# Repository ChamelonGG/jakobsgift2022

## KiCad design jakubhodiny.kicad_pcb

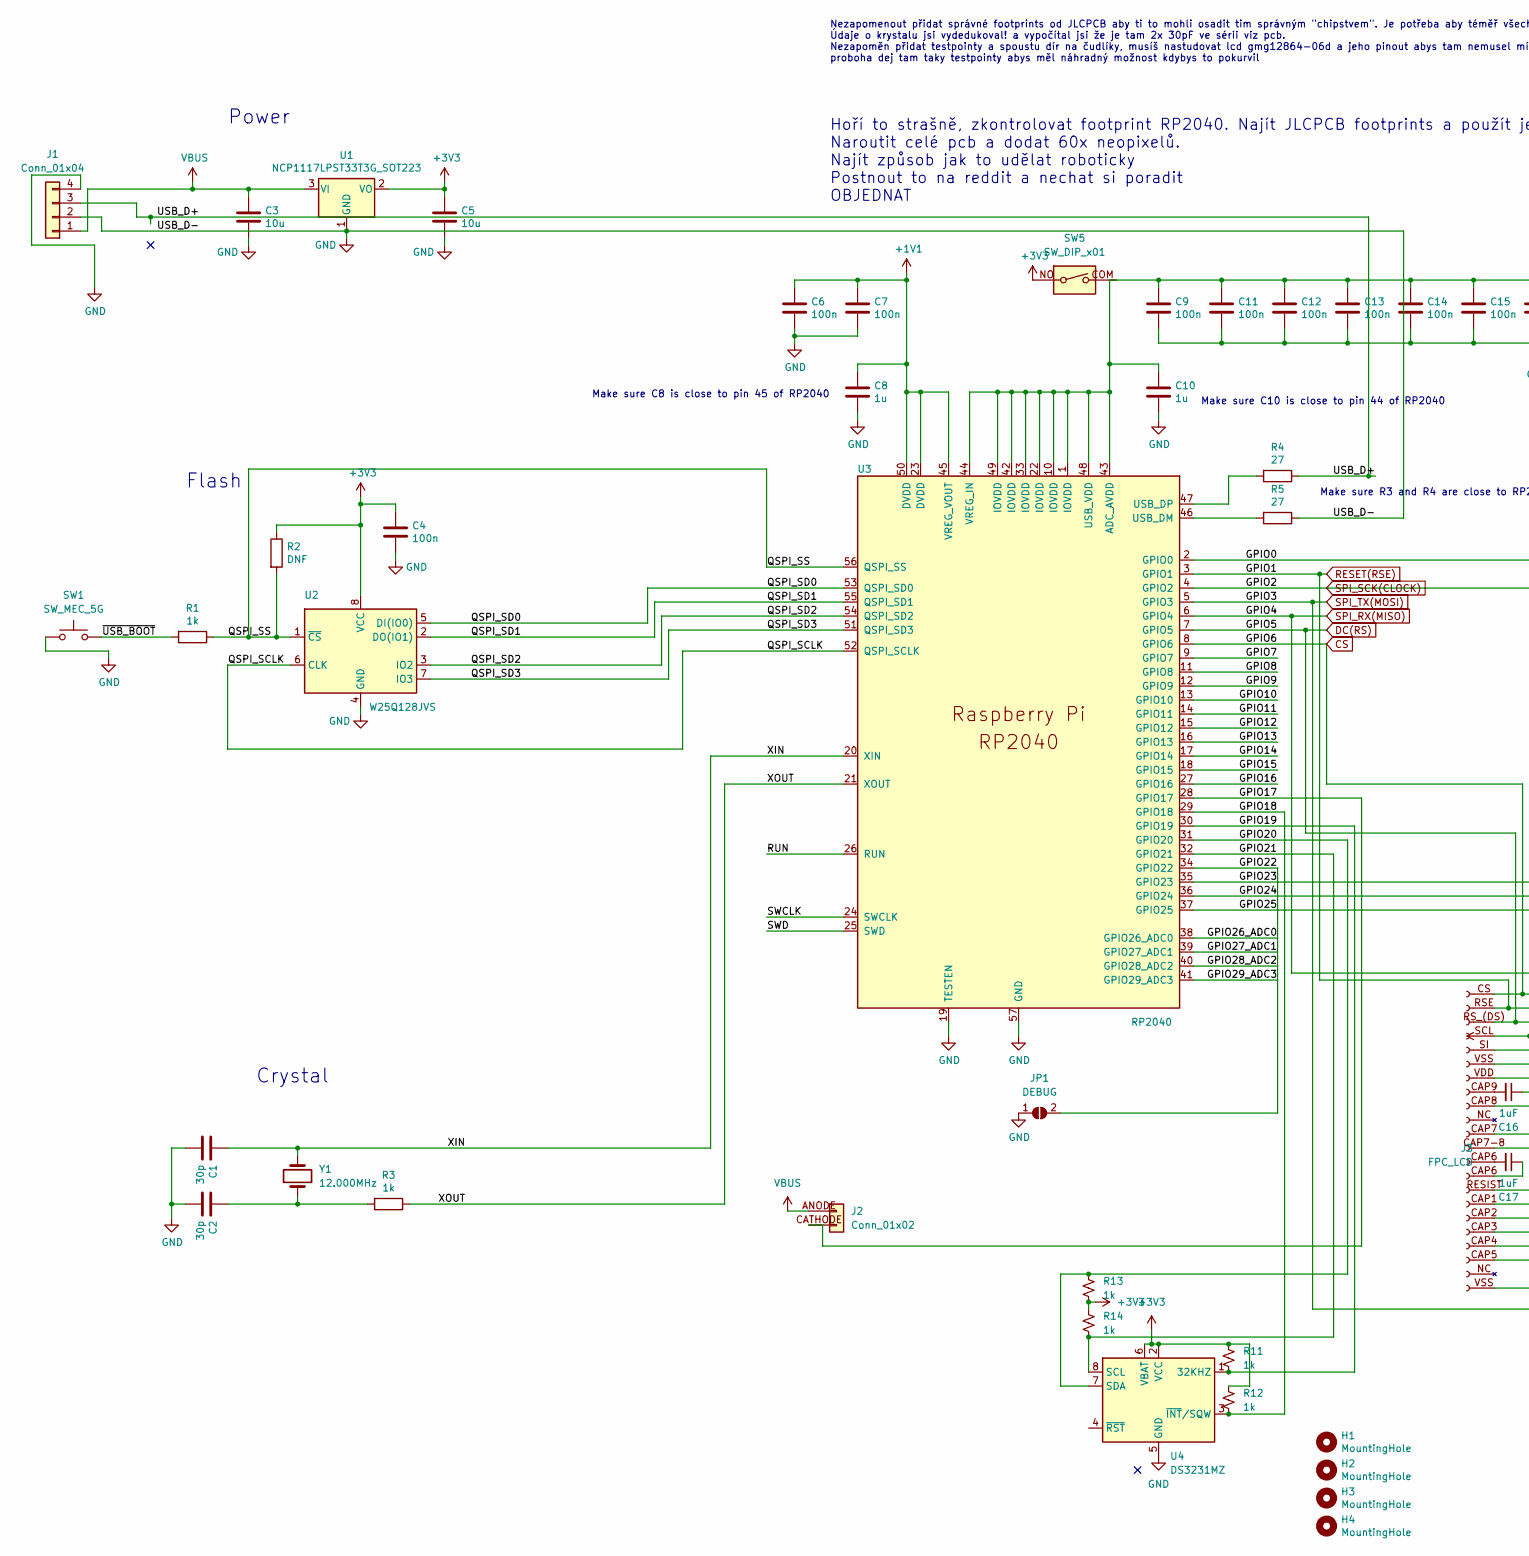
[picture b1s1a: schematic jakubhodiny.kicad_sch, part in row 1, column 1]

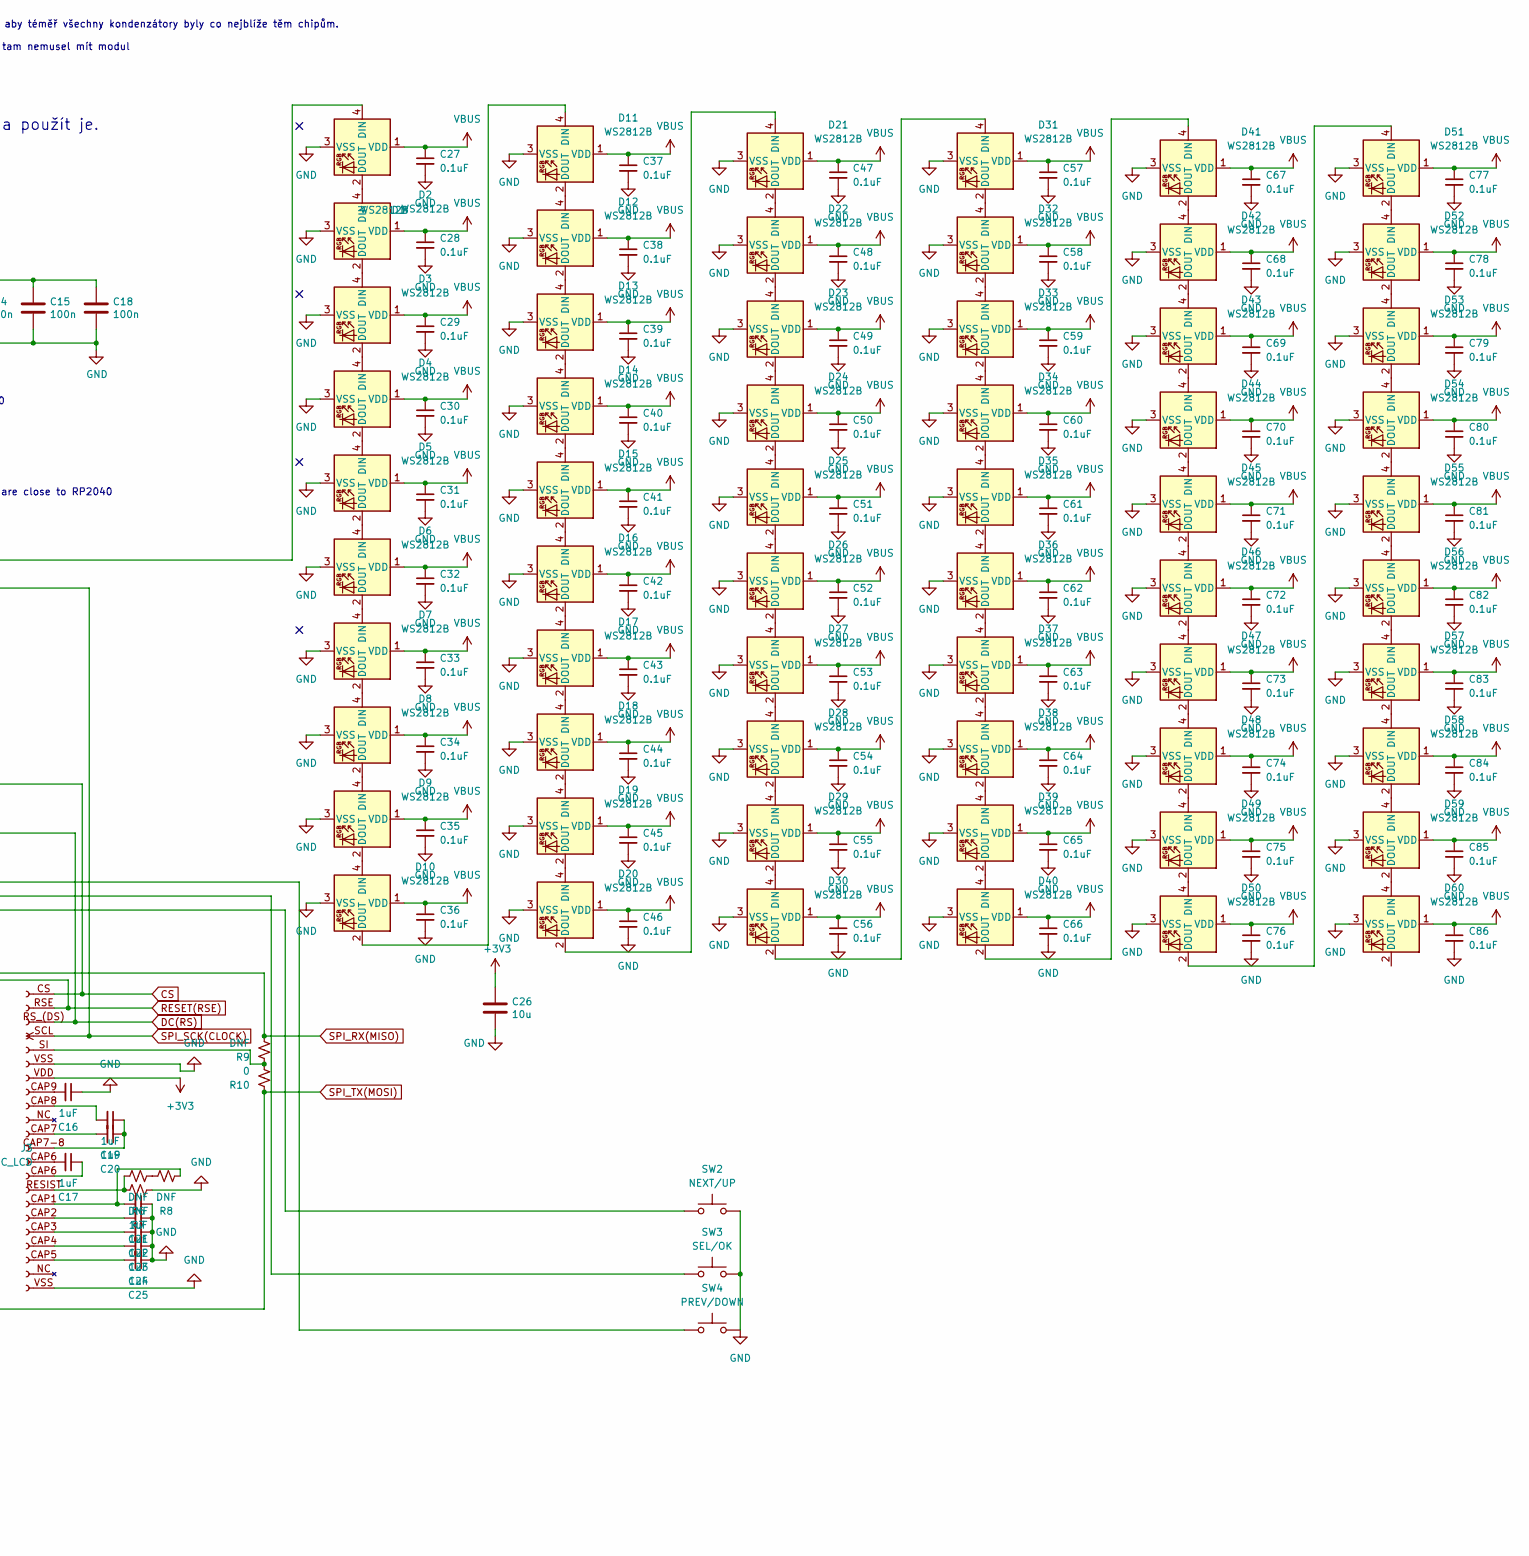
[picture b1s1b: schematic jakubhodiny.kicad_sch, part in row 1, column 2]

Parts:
C1, C2: 30p; C_0402_1005Metric
C3, C5, C26: 10u; C_0805_2012Metric
C4, C6, C7, C9, C11, C12, C13, C14, C15, C18: 100n; C_0402_1005Metric
C8, C10: 1u; C_0402_1005Metric
C16, C17, C19, C20, C21, C22, C23, C24, C25: 1uF; C_0402_1005Metric
C27, C28, C29, C30, C31, C32, C33, C34, C35, C36, C37, C38, C39, C40, C41, C42, C43, C44, C45, C46, C47, C48, C49, C50, C51, C52, C53, C54, C55, C56, C57, C58, C59, C60, C61, C62, C63, C64, C65, C66, C67, C68, C69, C70, C71, C72, C73, C74, C75, C76, C77, C78, C79, C80, C81, C82, C83, C84, C85, C86: 0.1uF; C_0402_1005Metric
D1, D2, D3, D4, D5, D6, D7, D8, D9, D10, D11, D12, D13, D14, D15, D16, D17, D18, D19, D20, D21, D22, D23, D24, D25, D26, D27, D28, D29, D30, D31, D32, D33, D34, D35, D36, D37, D38, D39, D40, D41, D42, D43, D44, D45, D46, D47, D48, D49, D50, D51, D52, D53, D54, D55, D56, D57, D58, D59, D60: WS2812B; LED_WS2812B_PLCC4_5.0x5.0mm_P3.2mm
H1, H2, H3, H4: MountingHole; MountingHole_2.7mm_M2.5
J1: Conn_01x04; PinHeader_1x04_P2.54mm_Horizontal
J2: Conn_01x02; BACKLIGHT_LCD
J3: FPC_LCD; FCP_LCD
JP1: DEBUG; SolderJumper-2_P1.3mm_Open_Pad1.0x1.5mm
R1, R3: 1k; C_0402_1005Metric
R2: DNF; C_0402_1005Metric
R4, R5: 27; C_0402_1005Metric
R6, R7, R8, R9: DNF; SolderJumper-2_P1.3mm_Open_Pad1.0x1.5mm
R10: 0; SolderJumper-2_P1.3mm_Bridged2Bar_Pad1.0x1.5mm
R11, R12, R13, R14: 1k; R_0402_1005Metric
SW1: SW_MEC_5G; SW_PUSH_6mm
SW2: NEXT/UP; SW_PUSH_6mm
SW3: SEL/OK; SW_PUSH_6mm
SW4: PREV/DOWN; SW_PUSH_6mm
SW5: SW_DIP_x01; pushswitch
U1: NCP1117LPST33T3G_SOT223; SOT-223-3_TabPin2
U2: W25Q128JVS; SOIC-8_5.23x5.23mm_P1.27mm
U3: RP2040; RP2040-QFN-56
U4: DS3231MZ; SOIC-8_3.9x4.9mm_P1.27mm
Y1: 12.000MHz; Crystal_SMD_HC49-SD_HandSoldering

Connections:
+1V1: C6.1, C7.1, C8.1, U3.23 (DVDD), U3.45 (VREG_VOUT), U3.50 (DVDD)
+3V3: C4.1, C5.1, C26.1, J3.VDD (16), R2.1, R11.1, R12.1, R13.1, R14.1, SW5.NO, U1.2 (VO), U2.8 (VCC), U4.2 (VCC), U4.6 (VBAT)
/GPIO0: D1.4 (DIN), U3.2 (GPIO0)
/GPIO7: U3.9 (GPIO7)
/GPIO8: U3.11 (GPIO8)
/GPIO9: U3.12 (GPIO9)
/GPIO10: U3.13 (GPIO10)
/GPIO11: U3.14 (GPIO11)
/GPIO12: U3.15 (GPIO12)
/GPIO13: U3.16 (GPIO13)
/GPIO14: U3.17 (GPIO14)
/GPIO15: U3.18 (GPIO15)
/GPIO16: U3.27 (GPIO16)
/GPIO17: J2.CATHODE (Pin_2), U3.28 (GPIO17)
/GPIO18: R12.2, U3.29 (GPIO18), U4.3 (~INT/SQW)
/GPIO19: R11.2, U3.30 (GPIO19), U4.1 (32KHZ)
/GPIO20: R13.2, U3.31 (GPIO20), U4.7 (SDA)
/GPIO21: R14.2, U3.32 (GPIO21), U4.8 (SCL)
/QSPI_SCLK: U2.6 (CLK), U3.52 (QSPI_SCLK)
/QSPI_SD0: U2.5 (DI(IO0)), U3.53 (QSPI_SD0)
/QSPI_SD1: U2.2 (DO(IO1)), U3.55 (QSPI_SD1)
/QSPI_SD2: U2.3 (IO2), U3.54 (QSPI_SD2)
/QSPI_SD3: U2.7 (IO3), U3.51 (QSPI_SD3)
/QSPI_SS: R1.1, R2.2, U2.1 (~CS), U3.56 (QSPI_SS)
/RUN: U3.26 (RUN)
/SWCLK: U3.24 (SWCLK)
/SWD: U3.25 (SWD)
/USB_D+: J1.3, R4.1
/XIN: C1.1, U3.20 (XIN), Y1.2
/XOUT: R3.1, U3.21 (XOUT)
/~USB_BOOT: R1.2, SW1.3 (B), SW1.4 (B)
CS: J3.CS (22), U3.8 (GPIO6)
DC(RS): J3.RS_(DS) (20), U3.7 (GPIO5)
GND: C1.2, C2.2, C3.2, C4.2, C5.2, C6.2, C7.2, C8.2, C9.2, C10.2, C11.2, C12.2, C13.2, C14.2, C15.2, C16.1, C18.2, C21.1, C22.1, C23.1, C24.1, C25.1, C26.2, C27.2, C28.2, C29.2, C30.2, C31.2, C32.2, C33.2, C34.2, C35.2, C36.2, C37.2, C38.2, C39.2, C40.2, C41.2, C42.2, C43.2, C44.2, C45.2, C46.2, C47.2, C48.2, C49.2, C50.2, C51.2, C52.2, C53.2, C54.2, C55.2, C56.2, C57.2, C58.2, C59.2, C60.2, C61.2, C62.2, C63.2, C64.2, C65.2, C66.2, C67.2, C68.2, C69.2, C70.2, C71.2, C72.2, C73.2, C74.2, C75.2, C76.2, C77.2, C78.2, C79.2, C80.2, C81.2, C82.2, C83.2, C84.2, C85.2, C86.2, D1.3 (VSS), D2.3 (VSS), D3.3 (VSS), D4.3 (VSS), D5.3 (VSS), D6.3 (VSS), D7.3 (VSS), D8.3 (VSS), D9.3 (VSS), D10.3 (VSS), D11.3 (VSS), D12.3 (VSS), D13.3 (VSS), D14.3 (VSS), D15.3 (VSS), D16.3 (VSS), D17.3 (VSS), D18.3 (VSS), D19.3 (VSS), D20.3 (VSS), D21.3 (VSS), D22.3 (VSS), D23.3 (VSS), D24.3 (VSS), D25.3 (VSS), D26.3 (VSS), D27.3 (VSS), D28.3 (VSS), D29.3 (VSS), D30.3 (VSS), D31.3 (VSS), D32.3 (VSS), D33.3 (VSS), D34.3 (VSS), D35.3 (VSS), D36.3 (VSS), D37.3 (VSS), D38.3 (VSS), D39.3 (VSS), D40.3 (VSS), D41.3 (VSS), D42.3 (VSS), D43.3 (VSS), D44.3 (VSS), D45.3 (VSS), D46.3 (VSS), D47.3 (VSS), D48.3 (VSS), D49.3 (VSS), D50.3 (VSS), D51.3 (VSS), D52.3 (VSS), D53.3 (VSS), D54.3 (VSS), D55.3 (VSS), D56.3 (VSS), D57.3 (VSS), D58.3 (VSS), D59.3 (VSS), D60.3 (VSS), J1.2, J1.4, J3.VSS (17), JP1.1 (A), R5.1, R7.2, SW1.1 (A), SW1.2 (A), SW2.3 (B), SW2.4 (B), SW3.3 (B), SW3.4 (B), SW4.3 (B), SW4.4 (B), U1.1 (GND), U2.4 (GND), U3.19 (TESTEN), U3.57 (GND), U4.5 (GND)
unnamed: C2.1, R3.2, Y1.1
unnamed: C9.1, C10.1, C11.1, C12.1, C13.1, C14.1, C15.1, C18.1, U3.1 (IOVDD), U3.10 (IOVDD), U3.22 (IOVDD), U3.33 (IOVDD), U3.42 (IOVDD), U3.43 (ADC_AVDD), U3.44 (VREG_IN), U3.48 (USB_VDD), U3.49 (IOVDD)
unnamed: C16.2, J3.CAP9 (15)
unnamed: C19.1, C20.1, J3.CAP7-8 (11)
unnamed: C19.2, J3.CAP8 (14)
unnamed: C20.2, J3.CAP7 (12)
unnamed: C21.2, J3.CAP1 (7), R8.2
unnamed: C22.2, J3.CAP2 (6)
unnamed: C23.2, J3.CAP3 (5)
unnamed: C24.2, J3.CAP4 (4)
unnamed: C25.2, J3.CAP5 (3)
unnamed: D1.2 (DOUT), D2.4 (DIN)
unnamed: D2.2 (DOUT), D3.4 (DIN)
unnamed: D3.2 (DOUT), D4.4 (DIN)
unnamed: D4.2 (DOUT), D5.4 (DIN)
unnamed: D5.2 (DOUT), D6.4 (DIN)
unnamed: D6.2 (DOUT), D7.4 (DIN)
unnamed: D7.2 (DOUT), D8.4 (DIN)
unnamed: D8.2 (DOUT), D9.4 (DIN)
unnamed: D10.2 (DOUT), D11.4 (DIN)
unnamed: D9.2 (DOUT), D10.4 (DIN)
unnamed: D11.2 (DOUT), D12.4 (DIN)
unnamed: D12.2 (DOUT), D13.4 (DIN)
unnamed: D13.2 (DOUT), D14.4 (DIN)
unnamed: D14.2 (DOUT), D15.4 (DIN)
unnamed: D15.2 (DOUT), D16.4 (DIN)
unnamed: D16.2 (DOUT), D17.4 (DIN)
unnamed: D17.2 (DOUT), D18.4 (DIN)
unnamed: D18.2 (DOUT), D19.4 (DIN)
unnamed: D19.2 (DOUT), D20.4 (DIN)
unnamed: D20.2 (DOUT), D21.4 (DIN)
unnamed: D21.2 (DOUT), D22.4 (DIN)
unnamed: D22.2 (DOUT), D23.4 (DIN)
unnamed: D23.2 (DOUT), D24.4 (DIN)
unnamed: D24.2 (DOUT), D25.4 (DIN)
unnamed: D25.2 (DOUT), D26.4 (DIN)
unnamed: D26.2 (DOUT), D27.4 (DIN)
unnamed: D27.2 (DOUT), D28.4 (DIN)
unnamed: D28.2 (DOUT), D29.4 (DIN)
unnamed: D29.2 (DOUT), D30.4 (DIN)
unnamed: D30.2 (DOUT), D31.4 (DIN)
unnamed: D31.2 (DOUT), D32.4 (DIN)
unnamed: D32.2 (DOUT), D33.4 (DIN)
unnamed: D33.2 (DOUT), D34.4 (DIN)
unnamed: D34.2 (DOUT), D35.4 (DIN)
unnamed: D35.2 (DOUT), D36.4 (DIN)
unnamed: D36.2 (DOUT), D37.4 (DIN)
unnamed: D37.2 (DOUT), D38.4 (DIN)
unnamed: D38.2 (DOUT), D39.4 (DIN)
unnamed: D39.2 (DOUT), D40.4 (DIN)
unnamed: D40.2 (DOUT), D41.4 (DIN)
unnamed: D41.2 (DOUT), D42.4 (DIN)
unnamed: D42.2 (DOUT), D43.4 (DIN)
unnamed: D43.2 (DOUT), D44.4 (DIN)
unnamed: D44.2 (DOUT), D45.4 (DIN)
unnamed: D45.2 (DOUT), D46.4 (DIN)
unnamed: D46.2 (DOUT), D47.4 (DIN)
unnamed: D47.2 (DOUT), D48.4 (DIN)
unnamed: D48.2 (DOUT), D49.4 (DIN)
unnamed: D49.2 (DOUT), D50.4 (DIN)
unnamed: D50.2 (DOUT), D51.4 (DIN)
unnamed: D51.2 (DOUT), D52.4 (DIN)
unnamed: D52.2 (DOUT), D53.4 (DIN)
unnamed: D53.2 (DOUT), D54.4 (DIN)
unnamed: D54.2 (DOUT), D55.4 (DIN)
unnamed: D55.2 (DOUT), D56.4 (DIN)
unnamed: D56.2 (DOUT), D57.4 (DIN)
unnamed: D57.2 (DOUT), D58.4 (DIN)
unnamed: D58.2 (DOUT), D59.4 (DIN)
unnamed: D59.2 (DOUT), D60.4 (DIN)
unnamed: J3.RESIST (8), R6.1, R7.1
unnamed: J3.SI (18), R9.1, R10.2
unnamed: R4.2, U3.47 (USB_DP)
unnamed: R5.2, U3.46 (USB_DM)
unnamed: R6.2, R8.1
RESET(RSE): J3.RSE (21), U3.3 (GPIO1)
SPI_RX(MISO): R9.2, U3.6 (GPIO4)
SPI_SCK(CLOCK): J3.SCL (19), U3.4 (GPIO2)
SPI_TX(MOSI): R10.1, U3.5 (GPIO3)
VBUS: C3.1, C27.1, C28.1, C29.1, C30.1, C31.1, C32.1, C33.1, C34.1, C35.1, C36.1, C37.1, C38.1, C39.1, C40.1, C41.1, C42.1, C43.1, C44.1, C45.1, C46.1, C47.1, C48.1, C49.1, C50.1, C51.1, C52.1, C53.1, C54.1, C55.1, C56.1, C57.1, C58.1, C59.1, C60.1, C61.1, C62.1, C63.1, C64.1, C65.1, C66.1, C67.1, C68.1, C69.1, C70.1, C71.1, C72.1, C73.1, C74.1, C75.1, C76.1, C77.1, C78.1, C79.1, C80.1, C81.1, C82.1, C83.1, C84.1, C85.1, C86.1, D1.1 (VDD), D2.1 (VDD), D3.1 (VDD), D4.1 (VDD), D5.1 (VDD), D6.1 (VDD), D7.1 (VDD), D8.1 (VDD), D9.1 (VDD), D10.1 (VDD), D11.1 (VDD), D12.1 (VDD), D13.1 (VDD), D14.1 (VDD), D15.1 (VDD), D16.1 (VDD), D17.1 (VDD), D18.1 (VDD), D19.1 (VDD), D20.1 (VDD), D21.1 (VDD), D22.1 (VDD), D23.1 (VDD), D24.1 (VDD), D25.1 (VDD), D26.1 (VDD), D27.1 (VDD), D28.1 (VDD), D29.1 (VDD), D30.1 (VDD), D31.1 (VDD), D32.1 (VDD), D33.1 (VDD), D34.1 (VDD), D35.1 (VDD), D36.1 (VDD), D37.1 (VDD), D38.1 (VDD), D39.1 (VDD), D40.1 (VDD), D41.1 (VDD), D42.1 (VDD), D43.1 (VDD), D44.1 (VDD), D45.1 (VDD), D46.1 (VDD), D47.1 (VDD), D48.1 (VDD), D49.1 (VDD), D50.1 (VDD), D51.1 (VDD), D52.1 (VDD), D53.1 (VDD), D54.1 (VDD), D55.1 (VDD), D56.1 (VDD), D57.1 (VDD), D58.1 (VDD), D59.1 (VDD), D60.1 (VDD), J1.1, J2.ANODE (Pin_1), U1.3 (VI)

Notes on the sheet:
Make sure C10 is close to pin 44 of RP2040
Crystal
Make sure R3 and R4 are close to RP2040
Flash
Nezapomenout přidat správné footprints od JLCPCB aby ti to mohli osadit tim správným "chipstvem". Je potřeba aby téměř všechny kondenzátory byly co nejblíže těm chipům. Údaje o krystalu jsi vydedukoval! a vypočítal jsi že je tam 2x 30pF ve sérii viz pcb. Nezapoměn přidat testpointy a spoustu dír na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
Make sure C8 is close to pin 45 of RP2040
Hoří to strašně, zkontrolovat footprint RP2040. Najít JLCPCB footprints a použít je. Naroutit celé pcb a dodat 60x neopixelů. Najít způsob jak to udělat roboticky Postnout to na reddit a nechat si poradit OBJEDNAT
Power

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
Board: 2 copper layers, 178 parts (0 on the bottom side), 105 nets, no tracks yet.

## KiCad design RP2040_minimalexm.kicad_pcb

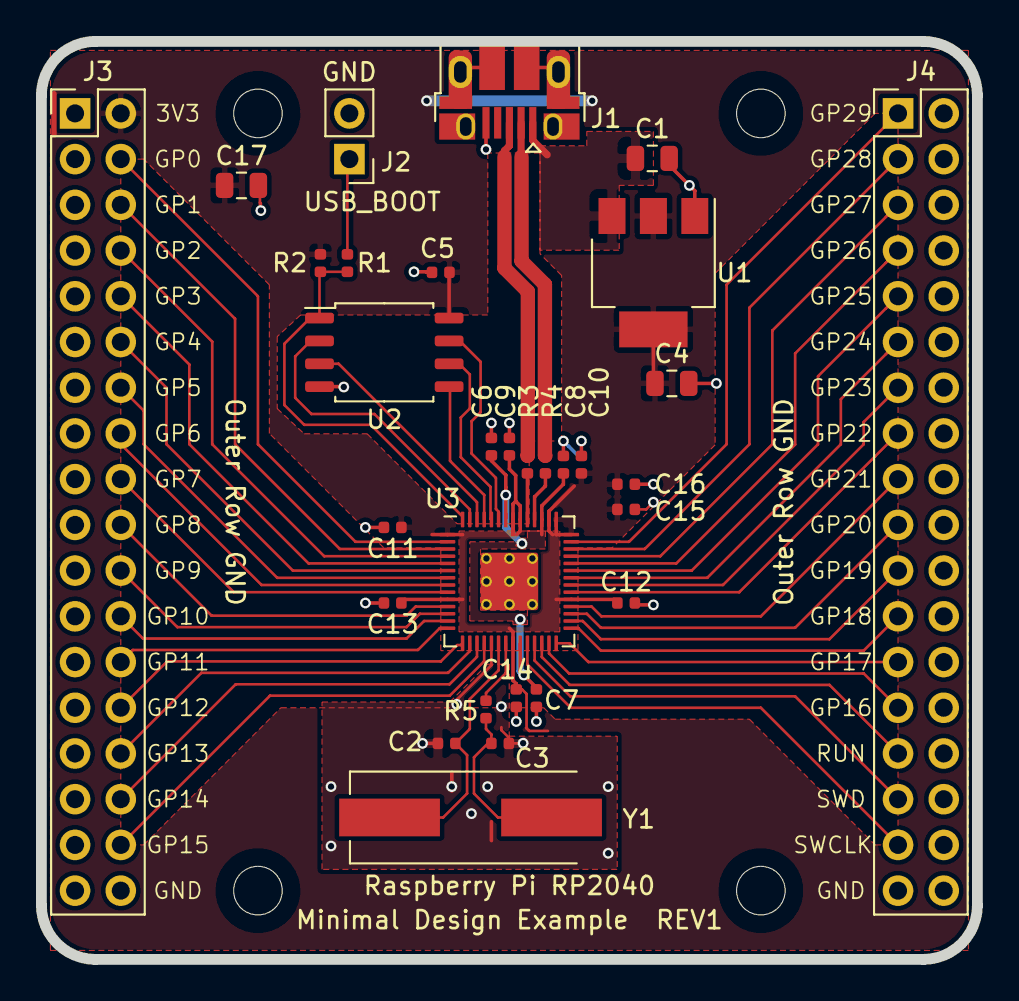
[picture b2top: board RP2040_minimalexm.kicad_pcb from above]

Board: 2 copper layers, 52.0 x 51.0 mm, 34 parts (0 on the bottom side), 51 nets.

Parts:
C1, C4, C17: 10u; C_0805_2012Metric
C2, C3: 27p; C_0402_1005Metric
C5, C6, C7, C9, C11, C12, C13, C14, C15, C16: 100n; C_0402_1005Metric
C8, C10: 1u; C_0402_1005Metric
H1, H2, H3, H4: MountingHole; MountingHole_2.7mm_M2.5
J1: USB_B_Micro; USB_Micro-B_Amphenol_10103594-0001LF_Horizontal_modified
J2: Conn_01x02; PinHeader_1x02_P2.54mm_Vertical
J3, J4: Conn_02x18_Odd_Even; PinHeader_2x18_P2.54mm_Vertical
R1, R5: 1k; C_0402_1005Metric
R2: DNF; C_0402_1005Metric
R3, R4: 27; C_0402_1005Metric
U1: NCP1117-3.3_SOT223; SOT-223-3_TabPin2
U2: W25Q128JVS; SOIC-8_5.23x5.23mm_P1.27mm
U3: RP2040; RP2040-QFN-56
Y1: ABLS-12.000MHZ-B4-T; Crystal_SMD_HC49-US

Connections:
+1V1: C6.1, C7.1, C8.1, U3.23, U3.45, U3.50
+3V3: C4.1, C5.1, C9.1, C10.1, C11.1, C12.1, C13.1, C14.1, C15.1, C16.1, C17.1, J3.2, R2.1, U1.2, U2.8, U3.1, U3.10, U3.22, U3.33, U3.42, U3.43, U3.44, U3.48, U3.49
/GPIO0: J3.4, U3.2
/GPIO1: J3.6, U3.3
/GPIO2: J3.8, U3.4
/GPIO3: J3.10, U3.5
/GPIO4: J3.12, U3.6
/GPIO5: J3.14, U3.7
/GPIO6: J3.16, U3.8
/GPIO7: J3.18, U3.9
/GPIO8: J3.20, U3.11
/GPIO9: J3.22, U3.12
/GPIO10: J3.24, U3.13
/GPIO11: J3.26, U3.14
/GPIO12: J3.28, U3.15
/GPIO13: J3.30, U3.16
/GPIO14: J3.32, U3.17
/GPIO15: J3.34, U3.18
/GPIO16: J4.27, U3.27
/GPIO17: J4.25, U3.28
/GPIO18: J4.23, U3.29
/GPIO19: J4.21, U3.30
/GPIO20: J4.19, U3.31
/GPIO21: J4.17, U3.32
/GPIO22: J4.15, U3.34
/GPIO23: J4.13, U3.35
/GPIO24: J4.11, U3.36
/GPIO25: J4.9, U3.37
/GPIO26_ADC0: J4.7, U3.38
/GPIO27_ADC1: J4.5, U3.39
/GPIO28_ADC2: J4.3, U3.40
/GPIO29_ADC3: J4.1, U3.41
/QSPI_SCLK: U2.6, U3.52
/QSPI_SD0: U2.5, U3.53
/QSPI_SD1: U2.2, U3.55
/QSPI_SD2: U2.3, U3.54
/QSPI_SD3: U2.7, U3.51
/QSPI_SS: R1.1, R2.2, U2.1, U3.56
/RUN: J4.29, U3.26
/SWCLK: J4.33, U3.24
/SWD: J4.31, U3.25
/USB_D+: J1.3, R3.1
/USB_D-: J1.2, R4.1
/XIN: C2.1, U3.20, Y1.1
/XOUT: R5.1, U3.21
/~USB_BOOT: J2.1, R1.2
GND: C1.2, C2.2, C3.2, C4.2, C5.2, C6.2, C7.2, C8.2, C9.2, C10.2, C11.2, C12.2, C13.2, C14.2, C15.2, C16.2, C17.2, J1.5, J1.6, J2.2, J3.1, J3.3, J3.5, J3.7, J3.9, J3.11, J3.13, J3.15, J3.17, J3.19, J3.21, J3.23, J3.25, J3.27, J3.29, J3.31, J3.33, J3.35, J3.36, J4.2, J4.4, J4.6, J4.8, J4.10, J4.12, J4.14, J4.16, J4.18, J4.20, J4.22, J4.24, J4.26, J4.28, J4.30, J4.32, J4.34, J4.35, J4.36, U1.1, U2.4, U3.19, U3.57
unnamed: C3.1, R5.2, Y1.2
unnamed: R3.2, U3.47
unnamed: R4.2, U3.46
VBUS: C1.1, J1.1, U1.3
